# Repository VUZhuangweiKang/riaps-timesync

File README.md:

# riaps-timesync

Time synchronization service, instrumentation and tests for the RIAPS platform.

## Time synchronization configuration tool: timesyncctl

The release (.deb) packages contain a configuration tool, called **timesyncctl** for an easy, semi-automated way for configuring a node for distributed time synchronization.
The tool configures and checks the status of the ChronoCape board (if needed) in the device tree and controls all services (`GPSd, chrony, phc2sys, ptp4l`, etc) needed
in a specific role.

Notes:

 - The tool is installed under `/opt/riaps/*<arch>*/bin`, where `*<arch>*` is either `armhf` or `amd64`. You should either make this directory part of your `PATH` or execute the tool with a full-path specification.

 - Some operations (`config` and `restart`) needs root priviledges, thus you need to run the tool as *root* or with the `sudo` command

The following time synchronization roles are supported:

 - **master**: the node is synchronized to (1) GPS (using the ChronoCape board) or (2) NTP (well-known internet server) or (3) NTP (the control/VM host) in this order. Selecting the best reference clock is automatic. It also acts as a PTP master on the local network.

 - **standalone**: same as master, but PTP master role is disabled.
 
 - **slave**: the node is forced to use PTP in slave mode. Needs a PTP master on the local network.

Running **timesyncctl**:

 - `timesyncctl config`: will list the available roles.
 - `timesyncctl config <role>`: will change the node's configuration for the given role and will restart the services. Needs root priviledges.
 - `timesyncctl restart`: will restart the services in the current role. Needs root priviledges.
 - `timesyncctl status`: check the status of the services and device tree in the current role.

Examples:

To configure the node for a master role:

    sudo /opt/riaps/armhf/bin/timesyncctl config master

To check if everything is as expected in the current role:

    /opt/riaps/armhf/bin/timesyncctl status

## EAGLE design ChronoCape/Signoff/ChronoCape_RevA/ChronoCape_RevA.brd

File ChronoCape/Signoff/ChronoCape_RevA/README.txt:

ChronoCape Rev. A

PCB DECRIPTION: 3.4in x 2.15in  (BBB cape shape, see outline gerber)
                4 LAYER PCB (.062 inches thickness) FR4

                Smallest line width and spacing 6/6 mils
                Smallest standard drill hole 13 mils
                Components/Silkscreen on top side
                Double side soldermask
                
PCB STACKUP:

    Stack Layer     Gerber Polarity Comment	
    -----------     --------------- -------
    1 (Top)         Positive        Component side (signal)
    2 (Inner 1)     Positive        Power (GND)
    3 (Inner 2)     Positive        Power
    4 (Bottom)      Positive        Solder side (signal)

FILES:

ChronoCape_RevA.topsilkscreen.ger - Top Silk Screen (component side)
ChronoCape_RevA.topsoldermask.ger - Top Solder stop mask (component side)
ChronoCape_RevA.toplayer.ger  - Top Copper (component side), Positive Polarity
ChronoCape_RevA.internalplane1.ger  - Inner Layer 1, Positive Polarity
ChronoCape_RevA.internalplane2.ger  - Inner Layer 2, Positive Polarity
ChronoCape_RevA.bottomlayer.ger  - Bottom Copper (solder side), Positive Polarity
ChronoCape_RevA.bottomsoldermask.ger - Bottom Solder stop mask (solder side)
ChronoCape_RevA.boardoutline.ger - Board outline

ChronoCape_RevA.drills.xln - NC Drill : 2.4, Abs, inches, leading zero supress, quad
ChronoCape_RevA.drills.dri - NC Drill info

ChronoCape_RevA.tcream.ger  - Top Side solder paste

ChronoCape_RevA_centroid.csv - Centroid / Pick & Place / XY data

QUESTIONS?
  Please contact Peter Volgyesi <peter.volgyesi@vanderbilt.edu>
  at 615.294.6520 with any problems or questions

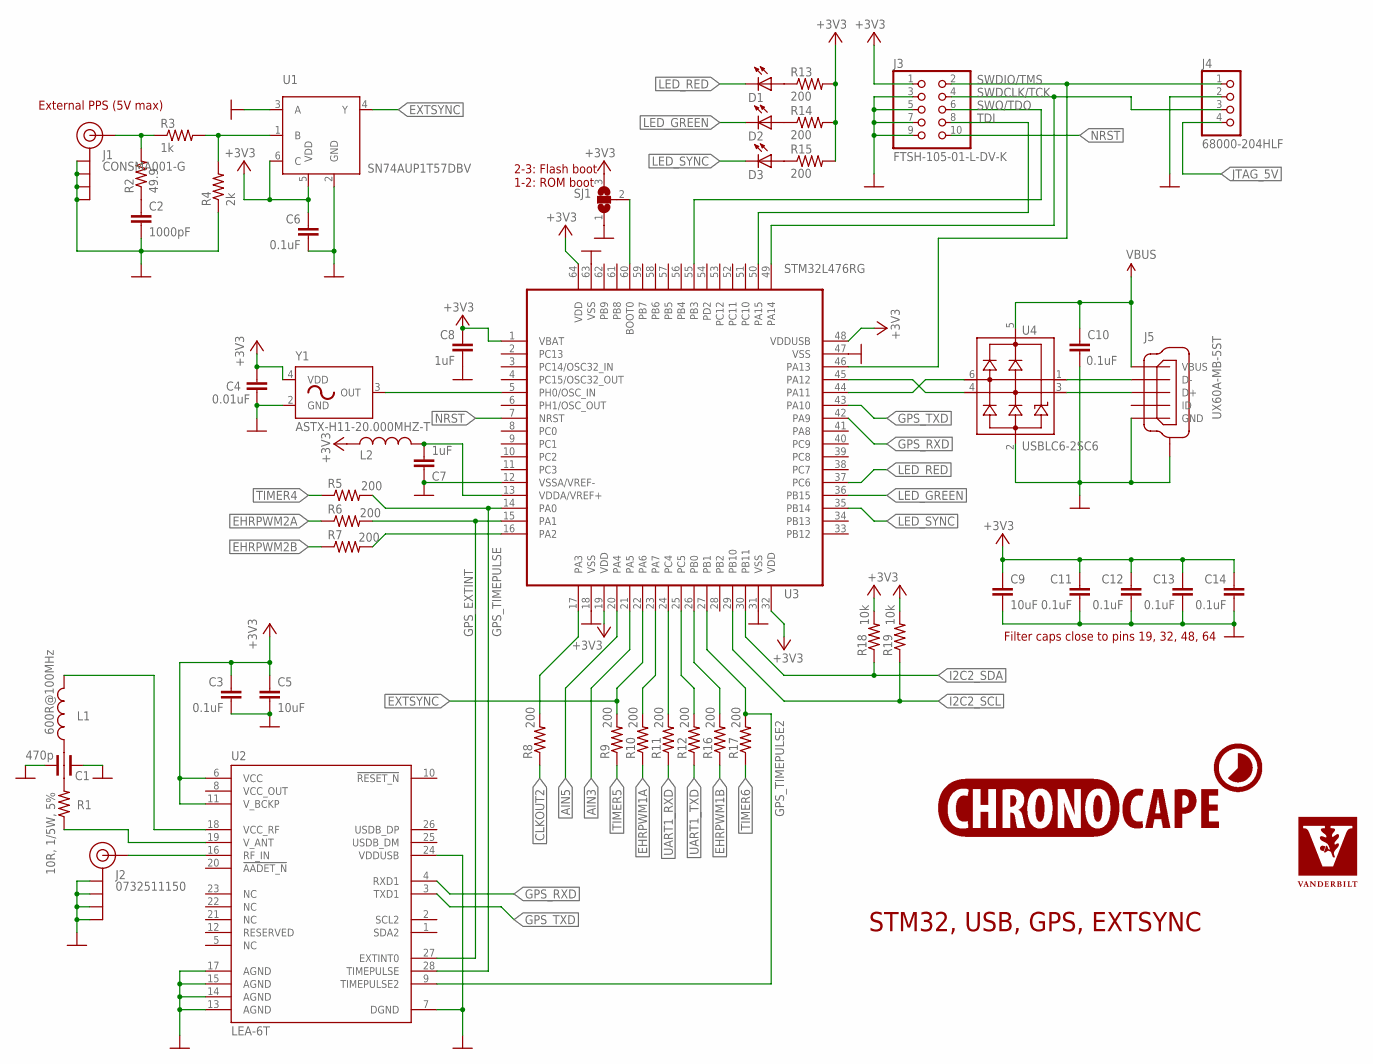
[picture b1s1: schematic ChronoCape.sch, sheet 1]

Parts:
C1: 470p; CTHROUGH0805
C2: 1000pF; CHIP0603
C3, C6, C10, C11, C12, C13, C14: 0.1uF; CHIP0603
C4: 0.01uF; CHIP0603
C5, C9: 10uF; CHIP0805
C7, C8: 1uF; CHIP0603
D1: 598-8010-107F; D0603
D2: 598-8070-107F; D0603
D3: 598-8030-107F; D0603
J1: CONSMA001-G; SMA-THROUGH
J2: 0732511150; SMA-EDGE
J3: FTSH-105-01-L-DV-K
J4: 68000-204HLF; 1X04
J5: UX60A-MB-5ST
L1: 600R@100MHz; CHIP0603
L2: BKP1608HS330; CHIP0603
LOGO1: LOGO_CHRONOCAPE; LOGO_CHRONOSCAPE
LOGO2: LOGO_VANDERBILT280MIL; LOGO_VANDERBILT_280MIL
R1: 10R, 1/5W, 5%; CHIP0603
R2: 49.9; CHIP0603
R3: 1k; CHIP0603
R4: 2k; CHIP0603
R5, R6, R7, R8, R9, R10, R11, R12, R13, R14, R15, R16, R17: 200; CHIP0603
R18, R19: 10k; CHIP0603
SJ1: SOLDERJUMPER_2WAYPASTE1&2; SJ_3_PASTE1&2
U1: SN74AUP1T57DBV; SOT23-6
U2: LEA-6T; LEA-6
U3: STM32L476RG; LQFP64
U4: USBLC6-2SC6; SOT23-6L
Y1: ASTX-H11-20.000MHZ-T; SMD_3.2X2.5

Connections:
+3V3: C3.1, C4.1, C5.1, C6.1, C8.1, C9.1, C11.1, C12.1, C13.1, C14.1, J3.1, L2.2, R13.2, R14.2, R15.2, R18.2, R19.2, SJ1.3, U1.5 (VDD), U1.6 (C), U2.6 (VCC), U2.11 (V_BCKP), U3.1 (VBAT), U3.19 (VDD), U3.32 (VDD), U3.48 (VDDUSB), U3.64 (VDD), Y1.4 (VDD); also elsewhere on the board
AIN3: U3.21 (PA5); also elsewhere on the board
AIN5: U3.20 (PA4); also elsewhere on the board
CLKOUT2: R8.1; also elsewhere on the board
EHRPWM1A: R10.1; also elsewhere on the board
EHRPWM1B: R16.1; also elsewhere on the board
EHRPWM2A: R6.1; also elsewhere on the board
EHRPWM2B: R7.1; also elsewhere on the board
EXTSYNC: R9.2, U1.4 (Y), U3.22 (PA6)
GND: C1.GND$1 (GND), C1.GND$2 (GND), C2.2, C3.2, C4.2, C5.2, C6.2, C7.1, C8.2, C9.2, C10.2, C11.2, C12.2, C13.2, C14.2, J1.GND@0 (GND), J1.GND@1 (GND), J1.GND@2 (GND), J1.GND@3 (GND), J2.GND@0 (GND), J2.GND@1 (GND), J2.GND@2 (GND), J2.GND@3 (GND), J3.3, J3.5, J3.7, J3.9, J4.2, J5.5 (GND), J5.SHLD@1 (SHLD), J5.SHLD@2 (SHLD), J5.SHLD@3 (SHLD), J5.SHLD@4 (SHLD), R4.1, SJ1.1, U1.2 (GND), U1.3 (A), U2.7 (DGND), U2.13 (AGND), U2.14 (AGND), U2.15 (AGND), U2.17 (AGND), U2.24 (VDDUSB), U3.12 (VSSA/VREF-), U3.18 (VSS), U3.31 (VSS), U3.47 (VSS), U3.63 (VSS), U4.2 (GND), Y1.2 (GND); also elsewhere on the board
GPS_EXTINT: R6.2, U2.27 (EXTINT0), U3.15 (PA1)
GPS_RXD: U2.4 (RXD1), U3.42 (PA9)
GPS_TIMEPULSE: R5.2, U2.28 (TIMEPULSE), U3.14 (PA0)
GPS_TIMEPULSE2: R17.2, U2.9 (TIMEPULSE2), U3.27 (PB1)
GPS_TXD: U2.3 (TXD1), U3.43 (PA10)
I2C2_SCL: R19.1, U3.29 (PB10); also elsewhere on the board
I2C2_SDA: R18.1, U3.30 (PB11); also elsewhere on the board
JTAG_5V: J4.4; also elsewhere on the board
LED_GREEN: D2.1 (C), U3.36 (PB15)
LED_RED: D1.1 (C), U3.37 (PC6)
LED_SYNC: D3.1 (C), U3.35 (PB14)
unnamed: C2.1, R2.1
unnamed: J1.SIG (SIGNAL), R2.2, R3.1
unnamed: C7.2, L2.1, U3.13 (VDDA/VREF+)
unnamed: R3.2, R4.2, U1.1 (B)
unnamed: D1.2 (A), R13.1
unnamed: D2.2 (A), R14.1
unnamed: L1.2, U2.18 (VCC_RF)
unnamed: D3.2 (A), R15.1
unnamed: J2.SIG (SIGNAL), U2.16 (RF_IN)
unnamed: C1.2, L1.1
unnamed: R1.1, U2.19 (V_ANT)
unnamed: C1.1, R1.2
unnamed: J5.2 (D-), U4.1 (IO1)
unnamed: SJ1.2, U3.60 (BOOT0)
unnamed: J5.3 (D+), U4.3 (IO2)
unnamed: R7.2, U3.16 (PA2)
unnamed: R10.2, U3.23 (PA7)
unnamed: R11.2, U3.24 (PC4)
unnamed: R12.2, U3.25 (PC5)
unnamed: R16.2, U3.26 (PB0)
unnamed: R8.2, U3.17 (PA3)
NRST: J3.10, U3.7 (NRST)
OUT: U3.5 (PH0/OSC_IN), Y1.3 (OUT)
SWDCLK/TCK: J3.4, J4.3, U3.49 (PA14)
SWDIO/TMS: J3.2, J4.1, U3.46 (PA13)
SWO/TDO: J3.6, U3.55 (PB3)
TDI: J3.8, U3.50 (PA15)
TIMER4: R5.1; also elsewhere on the board
TIMER5: R9.1; also elsewhere on the board
TIMER6: R17.1; also elsewhere on the board
UART1_RXD: R11.1; also elsewhere on the board
UART1_TXD: R12.1; also elsewhere on the board
USB_DM: U3.44 (PA11), U4.6 (IO1)
USB_DP: U3.45 (PA12), U4.4 (IO2)
VBUS: C10.1, J5.1 (VBUS), U4.5 (VBUS); also elsewhere on the board
VCC_OUT: U2.8 (VCC_OUT)

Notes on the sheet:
STM32, USB, GPS, EXTSYNC
2-3: Flash boot 1-2: ROM boot
External PPS (5V max)
Filter caps close to pins 19, 32, 48, 64

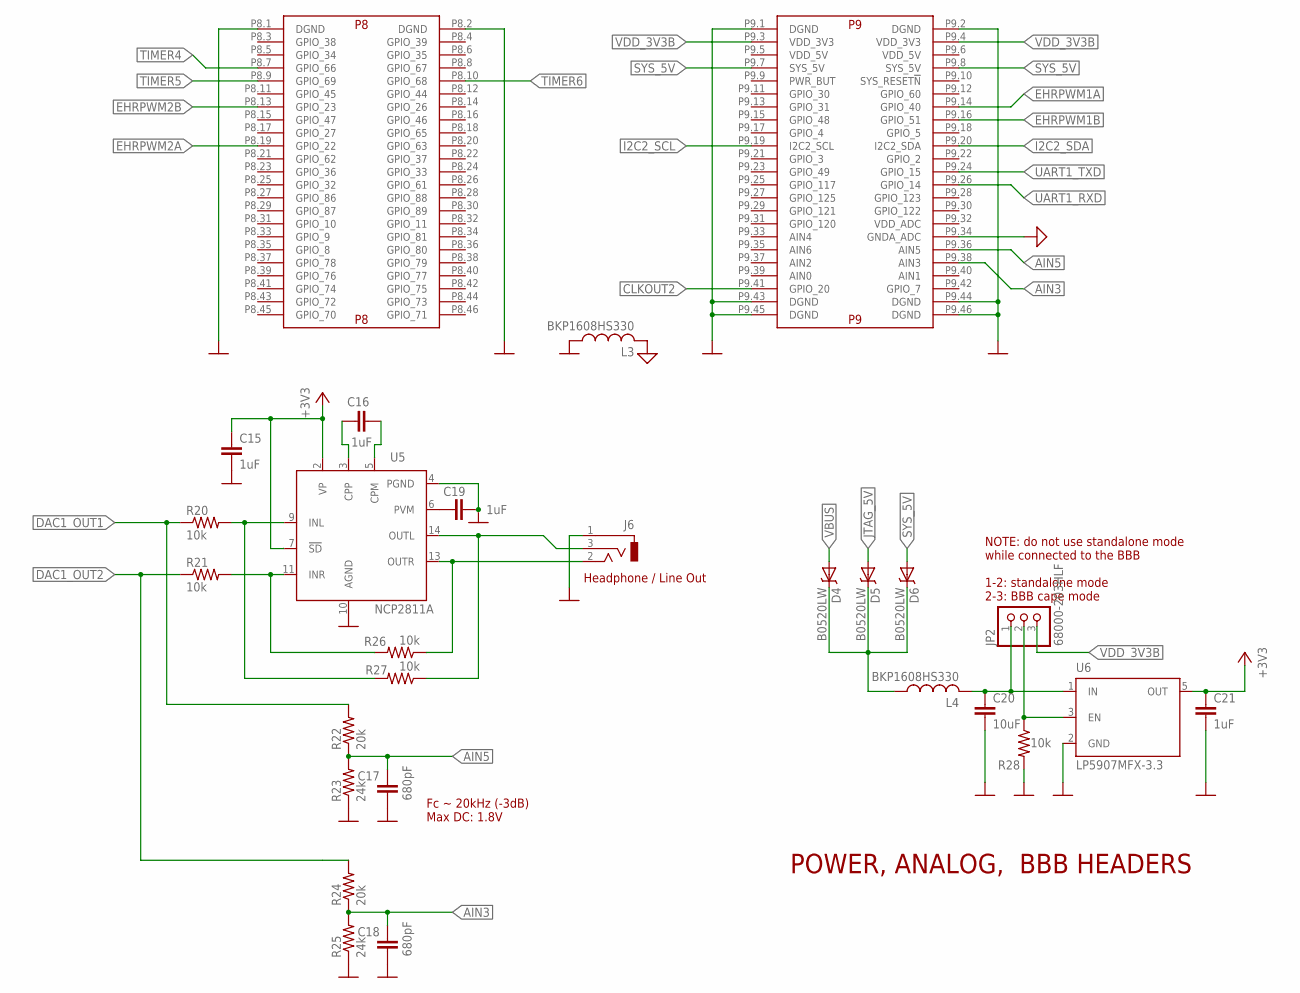
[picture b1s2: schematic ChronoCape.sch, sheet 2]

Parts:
BBB1: BEAGLE_BONE_BLACK_CAPE
C15, C16, C19, C21: 1uF; CHIP0603
C17, C18: 680pF; CHIP0603
C20: 10uF; CHIP0805
D4, D5, D6: B0520LW; SOD-123
J6: CON_STEREO_JACK_SJ-3523-SMT; SJ-3523-SMT
JP2: 68000-203HLF; 1X03
L3, L4: BKP1608HS330; CHIP0603
R20, R21, R26, R27, R28: 10k; CHIP0603
R22, R24: 20k; CHIP0603
R23, R25: 24k; CHIP0603
U5: NCP2811A; TSSOP14
U6: LP5907MFX-3.3; SOT23-5

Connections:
+3V3: C15.1, C21.1, U5.2 (VP), U5.7 (!SD), U6.5 (OUT); also elsewhere on the board
AGND: BBB1.P9.34 (GNDA_ADC), L3.2
AIN3: BBB1.P9.38 (AIN3), C18.1, R24.1, R25.2; also elsewhere on the board
AIN5: BBB1.P9.36 (AIN5), C17.1, R22.1, R23.2; also elsewhere on the board
CLKOUT2: BBB1.P9.41 (GPIO_20); also elsewhere on the board
DAC1_OUT1: R20.1, R22.2
DAC1_OUT2: R21.1, R24.2
EHRPWM1A: BBB1.P9.14 (GPIO_40); also elsewhere on the board
EHRPWM1B: BBB1.P9.16 (GPIO_51); also elsewhere on the board
EHRPWM2A: BBB1.P8.19 (GPIO_22); also elsewhere on the board
EHRPWM2B: BBB1.P8.13 (GPIO_23); also elsewhere on the board
GND: BBB1.P8.1 (DGND), BBB1.P8.2 (DGND), BBB1.P9.1 (DGND), BBB1.P9.2 (DGND), BBB1.P9.43 (DGND), BBB1.P9.44 (DGND), BBB1.P9.45 (DGND), BBB1.P9.46 (DGND), C15.2, C17.2, C18.2, C19.2, C20.2, C21.2, J6.1, L3.1, R23.1, R25.1, R28.2, U5.4 (PGND), U5.10 (AGND), U6.2 (GND); also elsewhere on the board
I2C2_SCL: BBB1.P9.19 (I2C2_SCL); also elsewhere on the board
I2C2_SDA: BBB1.P9.20 (I2C2_SDA); also elsewhere on the board
JTAG_5V: D5.A; also elsewhere on the board
unnamed: C20.1, JP2.1, L4.2, U6.1 (IN)
unnamed: D4.C, D5.C, D6.C, L4.1
unnamed: C16.1, U5.3 (CPP)
unnamed: C16.2, U5.5 (CPM)
unnamed: J6.2, R26.1, U5.13 (OUTR)
unnamed: R20.2, R27.2, U5.9 (INL)
unnamed: R21.2, R26.2, U5.11 (INR)
unnamed: J6.3, R27.1, U5.14 (OUTL)
PVM: C19.1, U5.6 (PVM)
PWR_EN: JP2.2, R28.1, U6.3 (EN)
SYS_5V: BBB1.P9.7 (SYS_5V), BBB1.P9.8 (SYS_5V), D6.A
TIMER4: BBB1.P8.7 (GPIO_66); also elsewhere on the board
TIMER5: BBB1.P8.9 (GPIO_69); also elsewhere on the board
TIMER6: BBB1.P8.10 (GPIO_68); also elsewhere on the board
UART1_RXD: BBB1.P9.26 (GPIO_14); also elsewhere on the board
UART1_TXD: BBB1.P9.24 (GPIO_15); also elsewhere on the board
VBUS: D4.A; also elsewhere on the board
VDD_3V3B: BBB1.P9.3 (VDD_3V3), BBB1.P9.4 (VDD_3V3), JP2.3

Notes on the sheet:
POWER, ANALOG, BBB HEADERS
Fc ~ 20kHz (-3dB) Max DC: 1.8V
Headphone / Line Out
NOTE: do not use standalone mode while connected to the BBB 1-2: standalone mode 2-3: BBB cape mode

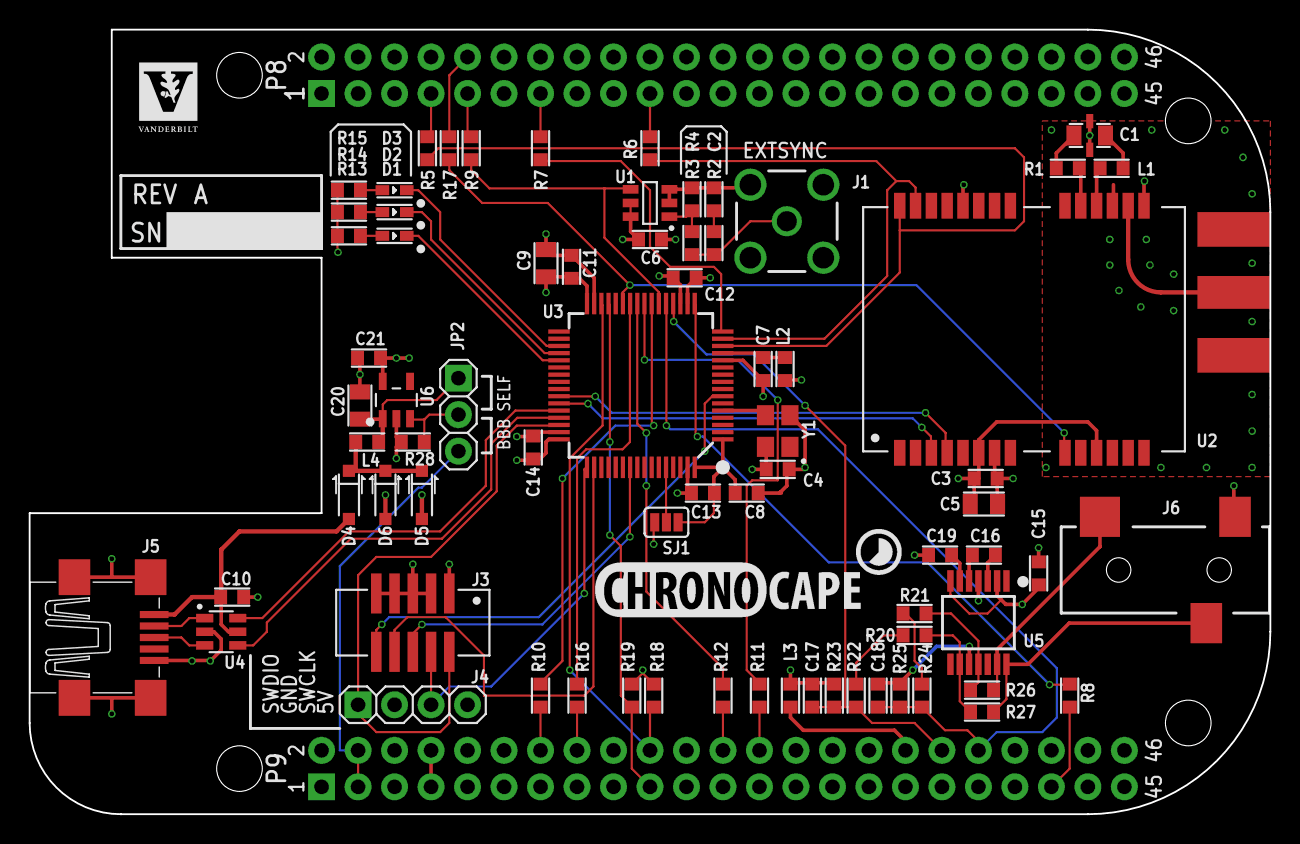
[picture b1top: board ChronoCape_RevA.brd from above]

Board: 4 copper layers, 86.4 x 54.6 mm, 77 parts (0 on the bottom side), 71 nets.

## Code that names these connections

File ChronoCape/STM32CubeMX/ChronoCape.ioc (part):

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Mcu.Name=STM32L476R(C-E-G)Tx
Mcu.Package=LQFP64
Mcu.UserName=STM32L476RGTx
PA0.GPIOParameters=GPIO_Label
PA0.GPIO_Label=TIMER4
PA0.Signal=S_TIM2_CH1_ETR
PA1.GPIOParameters=GPIO_Label
PA1.GPIO_Label=EHRPWM2A
PA1.Signal=S_TIM2_CH2
PA10.Mode=Asynchronous
PA10.Signal=USART1_RX
PA11.Mode=Device_Only
PA11.Signal=USB_OTG_FS_DM
PA12.Mode=Device_Only
PA12.Signal=USB_OTG_FS_DP
PA13.Mode=JTAG(4-pin)
PA13.Signal=SYS_JTMS-SWDIO
PA14.Mode=JTAG(4-pin)
PA14.Signal=SYS_JTCK-SWCLK
PA15.Mode=JTAG(4-pin)
PA15.Signal=SYS_JTDI
PA2.GPIOParameters=GPIO_Label
PA2.GPIO_Label=EHRPWM2B
PA2.Signal=S_TIM2_CH3
PA3.GPIOParameters=GPIO_Label
PA3.GPIO_Label=CLKOUT2
PA3.Signal=S_TIM2_CH4
PA4.GPIOParameters=GPIO_Label
PA4.GPIO_Label=AIN5
PA4.Signal=COMP_DAC11_group
PA5.GPIOParameters=GPIO_Label
PA5.GPIO_Label=AIN3
PA5.Signal=COMP_DAC12_group
PA6.GPIOParameters=GPIO_Label
PA6.GPIO_Label=TIMER5
PA6.Signal=S_TIM3_CH1
PA7.GPIOParameters=GPIO_Label
PA7.GPIO_Label=EHRPWM1A
PA7.Signal=S_TIM3_CH2
PA9.Mode=Asynchronous
PA9.Signal=USART1_TX
PB0.GPIOParameters=GPIO_Label
PB0.GPIO_Label=EHRPWM1B
PB0.Signal=S_TIM3_CH3
PB1.GPIOParameters=GPIO_Label
PB1.GPIO_Label=TIMER6
PB1.Signal=S_TIM3_CH4
PB10.GPIOParameters=GPIO_Label
PB10.GPIO_Label=I2C2_SCL
PB10.Mode=I2C
PB10.Signal=I2C2_SCL
PB11.GPIOParameters=GPIO_Label
PB11.GPIO_Label=I2C2_SDA
PB11.Mode=I2C
PB11.Signal=I2C2_SDA
PB14.GPIOParameters=GPIO_Label
PB14.GPIO_Label=LED_SYNC
PB14.Signal=GPIO_Output
PB15.GPIOParameters=GPIO_Label
PB15.GPIO_Label=LED_GREEN
PB15.Signal=GPIO_Output
PB3.Mode=JTAG(4-pin)
PB3.Signal=SYS_JTDO-SWO
PC4.GPIOParameters=GPIO_Label
PC4.GPIO_Label=UART1_RXD
PC4.Mode=Asynchronous
PC4.Signal=USART3_TX
PC5.GPIOParameters=GPIO_Label
PC5.GPIO_Label=UART1_TXD
PC5.Mode=Asynchronous
PC5.Signal=USART3_RX
PC6.GPIOParameters=GPIO_Label
PC6.GPIO_Label=LED_RED
PC6.Signal=GPIO_Output
PH0/OSC_IN.Mode=HSE-External-Clock-Source
PH0/OSC_IN.Signal=RCC_OSC_IN
RCC.HSE_VALUE=20000000
RCC.SYSCLKFreq_VALUE=50000000
RCC.SYSCLKSource=RCC_SYSCLKSOURCE_PLLCLK

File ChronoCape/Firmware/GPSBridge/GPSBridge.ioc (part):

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Mcu.Name=STM32L476R(C-E-G)Tx
Mcu.Package=LQFP64
Mcu.UserName=STM32L476RGTx
PA0.GPIOParameters=GPIO_Label
PA0.GPIO_Label=GPS_TIMEPULSE
PA0.Signal=GPXTI0
PA1.GPIOParameters=GPIO_Label
PA1.GPIO_Label=GPS_EXTINT
PA1.Signal=GPIO_Output
PA10.GPIOParameters=GPIO_Label
PA10.GPIO_Label=GPS_TXD
PA10.Mode=Asynchronous
PA10.Signal=USART1_RX
PA11.Mode=Device_Only
PA11.Signal=USB_OTG_FS_DM
PA12.Mode=Device_Only
PA12.Signal=USB_OTG_FS_DP
PA13.Mode=Serial_Wire
PA13.Signal=SYS_JTMS-SWDIO
PA14.Mode=Serial_Wire
PA14.Signal=SYS_JTCK-SWCLK
PA9.GPIOParameters=GPIO_Label
PA9.GPIO_Label=GPS_RXD
PA9.Mode=Asynchronous
PA9.Signal=USART1_TX
PB14.GPIOParameters=GPIO_Label
PB14.GPIO_Label=LED_SYNC
PB14.Signal=GPIO_Output
PB15.GPIOParameters=GPIO_Label
PB15.GPIO_Label=LED_GREEN
PB15.Signal=GPIO_Output
PC4.GPIOParameters=GPIO_Label
PC4.GPIO_Label=UART1_RXD
PC4.Mode=Asynchronous
PC4.Signal=USART3_TX
PC5.GPIOParameters=GPIO_Label
PC5.GPIO_Label=UART1_TXD
PC5.Mode=Asynchronous
PC5.Signal=USART3_RX
PC6.GPIOParameters=GPIO_Label
PC6.GPIO_Label=LED_RED
PC6.Signal=GPIO_Output
PH0/OSC_IN.Mode=HSE-External-Clock-Source
PH0/OSC_IN.Signal=RCC_OSC_IN
RCC.HSE_VALUE=20000000
RCC.SYSCLKFreq_VALUE=80000000
RCC.SYSCLKSource=RCC_SYSCLKSOURCE_PLLCLK
board=GPSBridge

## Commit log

2016-10-04 ChronoCape RevA board design
2016-10-10 Fixing device tree source
2016-10-10 Config files added for the image
2016-10-11 added chrony socket comm debugger tool
2016-10-11 Updated config for automatic fallback to NTP
2016-12-12 new cmake-based riap_ts library
2016-12-17 first signs of chrony comm
2016-12-18 fixing string conversion
2016-12-18 minor reorg
2016-12-18 clean-up warnings
2016-12-18 working baseline API
2016-12-18 print role and reference
2016-12-19 Added installation step
2016-12-19 fixing tv_sec to 32 bits
2016-12-19 added python wrapper module
2016-12-20 baseline python test
2017-01-09 Added a space to make a change - testing jenkins build on change commits
2017-03-14 simple GPIO timesync test
2017-03-14 minor fixes
2017-03-14 better handling of clock jumps
2017-03-20 minimum pulse width
2017-03-20 CubeMX update
2017-03-28 makefile for tools
2017-03-28 cross-compiling support
2017-03-28 add travis ci
2017-03-28 cleanup
2017-03-28 fixing glob pattern
2017-03-29 Python and config file releases
2017-03-29 Add travis status badge
2017-03-29 fixing python building dependencies
2017-03-29 fixing tar
2017-03-29 fixing build dir name
2017-03-29 upgrade setuptools for travis
2017-03-29 last try w/ setuptools for travis
2017-03-29 Fixing deployment
2017-03-29 architecture specific deb packages
2017-03-29 Release file descriptions.
2017-03-30 wip: decreasing scheduling effect
2017-03-30 decreasing scheduling jitter
2017-03-30 typos
2017-04-02 GPIO benchmarking
2017-04-02 updated configs based on timesync testing
2017-04-05 updated timesync config based on initial tests
2017-04-05 waking up in-between second boundaries
2017-04-05 fixing ownership of timesync config files
2017-04-06 updated timesync config based on initial test
2017-04-06 arbitrary phase, better logging
2017-04-06 memory-mapped GPIO option
2017-04-06 proper handling of the phase
2017-04-06 half second phase
2017-04-06 enable ChronoCape on all nodes
2017-04-07 prevent ptp4l to start before networking is up
2017-04-07 initial measurement logs and processing
2017-04-07 add the mmap option for gpio timing
2017-04-19 analog signal generator using PWM
2017-04-24 using absolute time for better sampling
2017-05-24 Experimenting with posix clock sources
2017-05-30 tsman: timesync manager initial commit
2017-05-31 Implementing tsman restart
2017-05-31 Implementing tsman config
2017-05-31 No more config.tgz
2017-05-31 Add slave role to config db
2017-05-31 Ready for 1.1.0
2017-06-01 Another twist on the build and packaging machinery
2017-06-01 skip python packages for now
2017-06-01 Removing deprecated docs
2017-06-01 travis fixes
2017-06-02 fixing travis deploy bug
2017-06-05 Brief documentation on tsman
2017-06-22 Update riaps-timesync-amd64.control
    Corrected architecture of riaps-externals dependency
2017-08-09 Message adjustment
2017-08-14 cleaning up generated/copied artifacts
2017-09-29 Add VU License Files
2017-09-29 Update LICENSE
    Width Adjustment
2017-10-09 logrotate policy for preventing large timesync log files
2017-11-15 simple benchmark code
2017-11-16 Summary of BBB python benchmarks
2017-11-16 benchmark result logs
2017-11-21 Adding log cleanup
2017-11-28 new sync generator tool
2017-11-28 remove unused argparse
2017-11-28 missing Makefile
2017-11-29 simplified Makefile to avoid build loops
2017-11-30 improved width and frequency compliance
2017-12-06 assert time estimation bugfix
2018-01-08 Fixing log rotation/quota problem
2018-01-09 Version Bump
2018-01-16 add ntp-standalone profile for VM development
2018-01-24 Bump version
2018-02-08 Update REAMDE.md w/ ntp-standalone profile
2018-03-08 enable discrete time offset step for >1s differences
2018-03-27 Add USR1-USR3 to pin name options
    Excluded USR0 since it is typically used to show network activity and should not be used by applications.
2018-06-18 new master role, no external timesync
2018-06-18 updating version for next bugfix release
2018-06-18 New master role explanation.
2018-07-13 Adjust 'master' configuration setup (#7)
    * Update Master hook to not test for ChronoCape
    * Update version.sh
    * Updating to be master mode
    * Update version.sh
    * Update ptp4l.conf
    * Updating soft link
2018-08-07 Switch to Jenkins build pipeline (#8)
    * Create Jenkinsfile
    * Jenkins deploy on tags
    * Remove Travis deploy
2018-08-07 Clean up old Jenkins builds
2018-08-31 increasing tx_timestamp_timeout due to sporadic errors on testbed
2018-08-31 bumping version
2018-09-25 Updated license to Apache 2.0
2018-10-08 riaps-externals is not a dependency, anymore
2018-10-10 Updated timesync structure and names
2018-10-11 simplifying timesync roles
2018-10-11 timesyncd initial draft
2018-10-12 first working version of timesyncd
2018-10-15 more robust ctrl_host handling
2018-10-15 remove stale capemgr from slave
2018-10-16 missing allow * directive from chrony.conf
2018-10-16 modified service dependency for 18.04
2018-10-16 disable gpsd by default
2018-10-16 better handling status
2018-10-17 Squashed commit of the following:
    commit 3d21691bf20924ab4309b8bc2d6729db7f2f596a
    Author: Peter Volgyesi <peter.volgyesi@gmail.com>
    Date: Tue Oct 16 22:02:11 2018 +0000
    better handling status
    commit 4ea89de61c32871ad09cb7a81004e1a9c06b1ee4
    Author: Peter Volgyesi <peter.volgyesi@gmail.com>
2018-10-29 Update version (#9)
    Changing riaps-pycom release, need to bump up this version number
2018-12-03 Update README.md (#10)
    GPS master role no longer available, changed example
2018-12-20 Bumping version for 1.1.12 release
    No changes occurred in timesync. Bumping for version to match other RIAPS platform repositories
2019-05-23 Added Doxygen documentation
2019-06-18 Add sphinx document translation
2019-06-18 Use cmake for documentation
2019-06-18 Move to build dir for cmake doc build
2019-06-18 Add make build dir
2019-06-18 Moved documentation to readthedocs (#12)
    * Add Doxyfile to use for readthedoc (instead of doxyfile.in with cmake, not supported by readthedoc)
    * Use doxygen instead of cmake
    * html location update
    * Add breathe tool
    * Add version
    * Indicate breathe location
2019-07-01 Update version number for v1.1.16 release. (#13)

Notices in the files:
parts and their libraries:
EAGLENEST: Copyright (C) 2012-2015 Vanderbilt University, ISIS
